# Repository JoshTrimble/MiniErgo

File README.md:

This design was inspired by the Gboards' GergoPlex. I wanted to take the base design and tweak it to be a smaller form factor, while maintaining the layout as much as possible. This board is driven by 2 Xiao Seeed Studio RP2040s and includes hot swappable sockets for Kailh Choc switches. The PCB is designed yp be double sided with the left side having the micro control placed upside down via standoffs.

One other thing to note; Because of the minimal footprint achieved, there might be a very slight overhang of the outer hot swap socket solder points and the edge of the board depending on the hot swap sockets used. There should be plenty of room for contact of the PCB tracks to the socket, and the excess can be sanded down to be flush with the PCB if desired. From my testing, you can't even notice. This design might be changed in future versions of the board. (P.S. Know that sanding PCBs can be hazardous. Please take procautions if you choose to sand anything attached to the board)

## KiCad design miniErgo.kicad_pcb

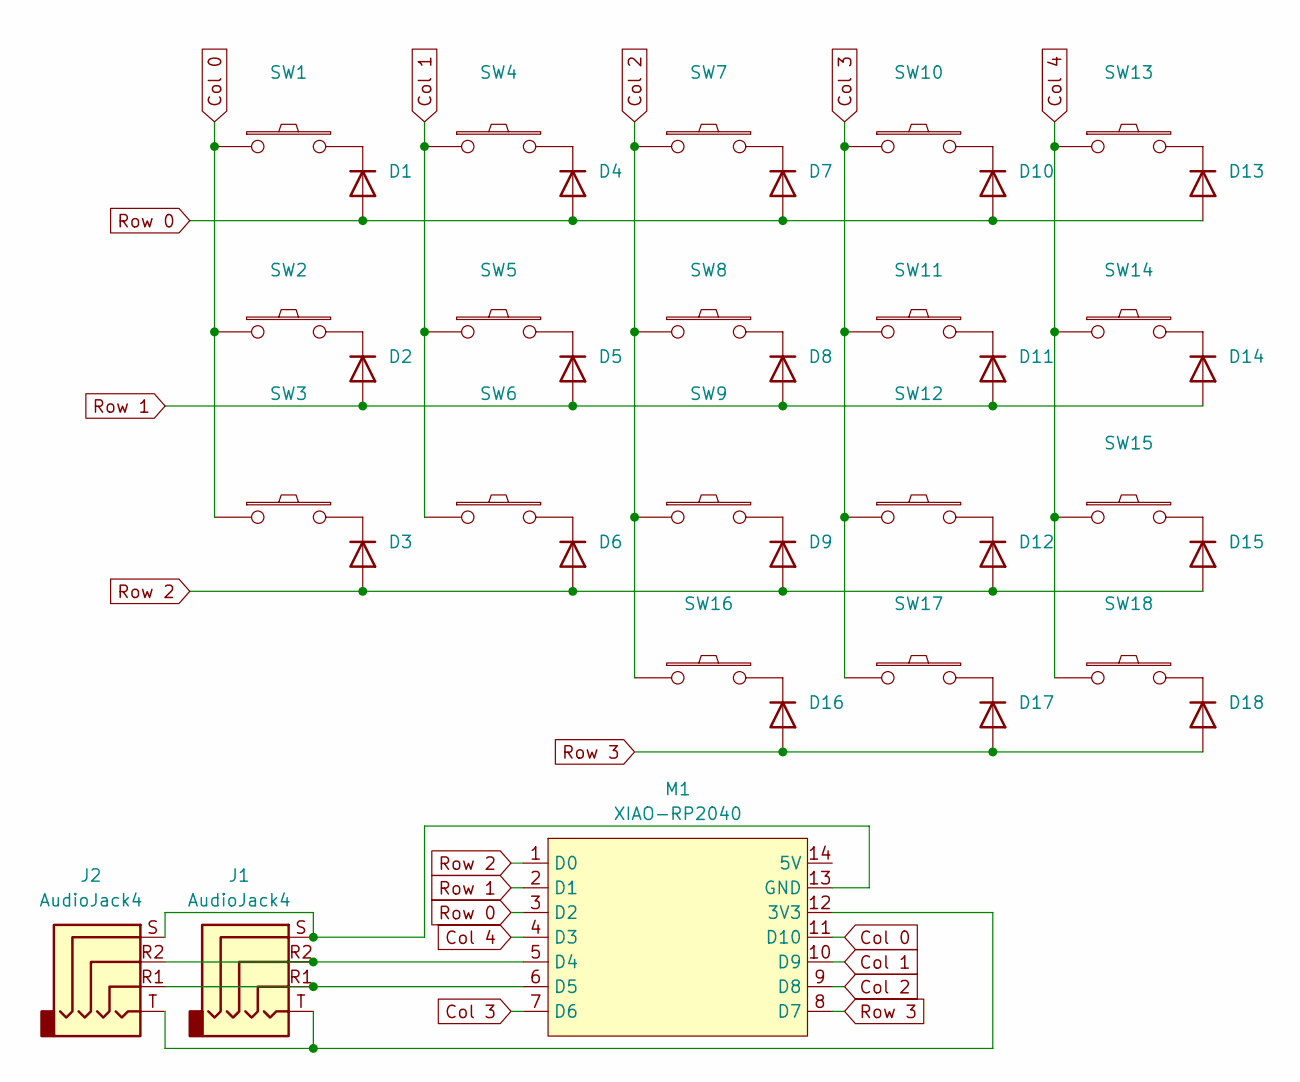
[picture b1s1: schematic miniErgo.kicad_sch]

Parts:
D1, D2, D3, D4, D5, D6, D7, D8, D9, D10, D11, D12, D13, D14, D15, D16, D17, D18: SOD-123F Double Sided
J1, J2: AudioJack4; TRRS-PJ-320A
M1: XIAO-RP2040
SW1, SW2, SW3, SW4, SW5, SW6, SW7, SW8, SW9, SW10, SW11, SW12, SW13, SW14, SW15, SW16, SW17, SW18: Kailh Choch HS Double Sided

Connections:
Col 0: M1.11 (D10), SW1.1, SW2.1, SW3.1
Col 1: M1.10 (D9), SW4.1, SW5.1, SW6.1
Col 2: M1.9 (D8), SW7.1, SW8.1, SW9.1, SW16.1
Col 3: M1.7 (D6), SW10.1, SW11.1, SW12.1, SW17.1
Col 4: M1.4 (D3), SW13.1, SW14.1, SW15.1, SW18.1
unnamed: D1.1 (K), SW1.2
unnamed: D2.1 (K), SW2.2
unnamed: D3.1 (K), SW3.2
unnamed: D4.1 (K), SW4.2
unnamed: D5.1 (K), SW5.2
unnamed: D6.1 (K), SW6.2
unnamed: D7.1 (K), SW7.2
unnamed: D8.1 (K), SW8.2
unnamed: D9.1 (K), SW9.2
unnamed: D10.1 (K), SW10.2
unnamed: D11.1 (K), SW11.2
unnamed: D12.1 (K), SW12.2
unnamed: D13.1 (K), SW13.2
unnamed: D14.1 (K), SW14.2
unnamed: D15.1 (K), SW15.2
unnamed: D16.1 (K), SW16.2
unnamed: D17.1 (K), SW17.2
unnamed: D18.1 (K), SW18.2
unnamed: J1.R1, J2.R1, M1.6 (D5)
unnamed: J1.R2, J2.R2, M1.5 (D4)
unnamed: J1.S, J2.S, M1.13 (GND)
unnamed: J1.T, J2.T, M1.12 (3V3)
Row 0: D1.2 (A), D4.2 (A), D7.2 (A), D10.2 (A), D13.2 (A), M1.3 (D2)
Row 1: D2.2 (A), D5.2 (A), D8.2 (A), D11.2 (A), D14.2 (A), M1.2 (D1)
Row 2: D3.2 (A), D6.2 (A), D9.2 (A), D12.2 (A), D15.2 (A), M1.1 (D0)
Row 3: D16.2 (A), D17.2 (A), D18.2 (A), M1.8 (D7)

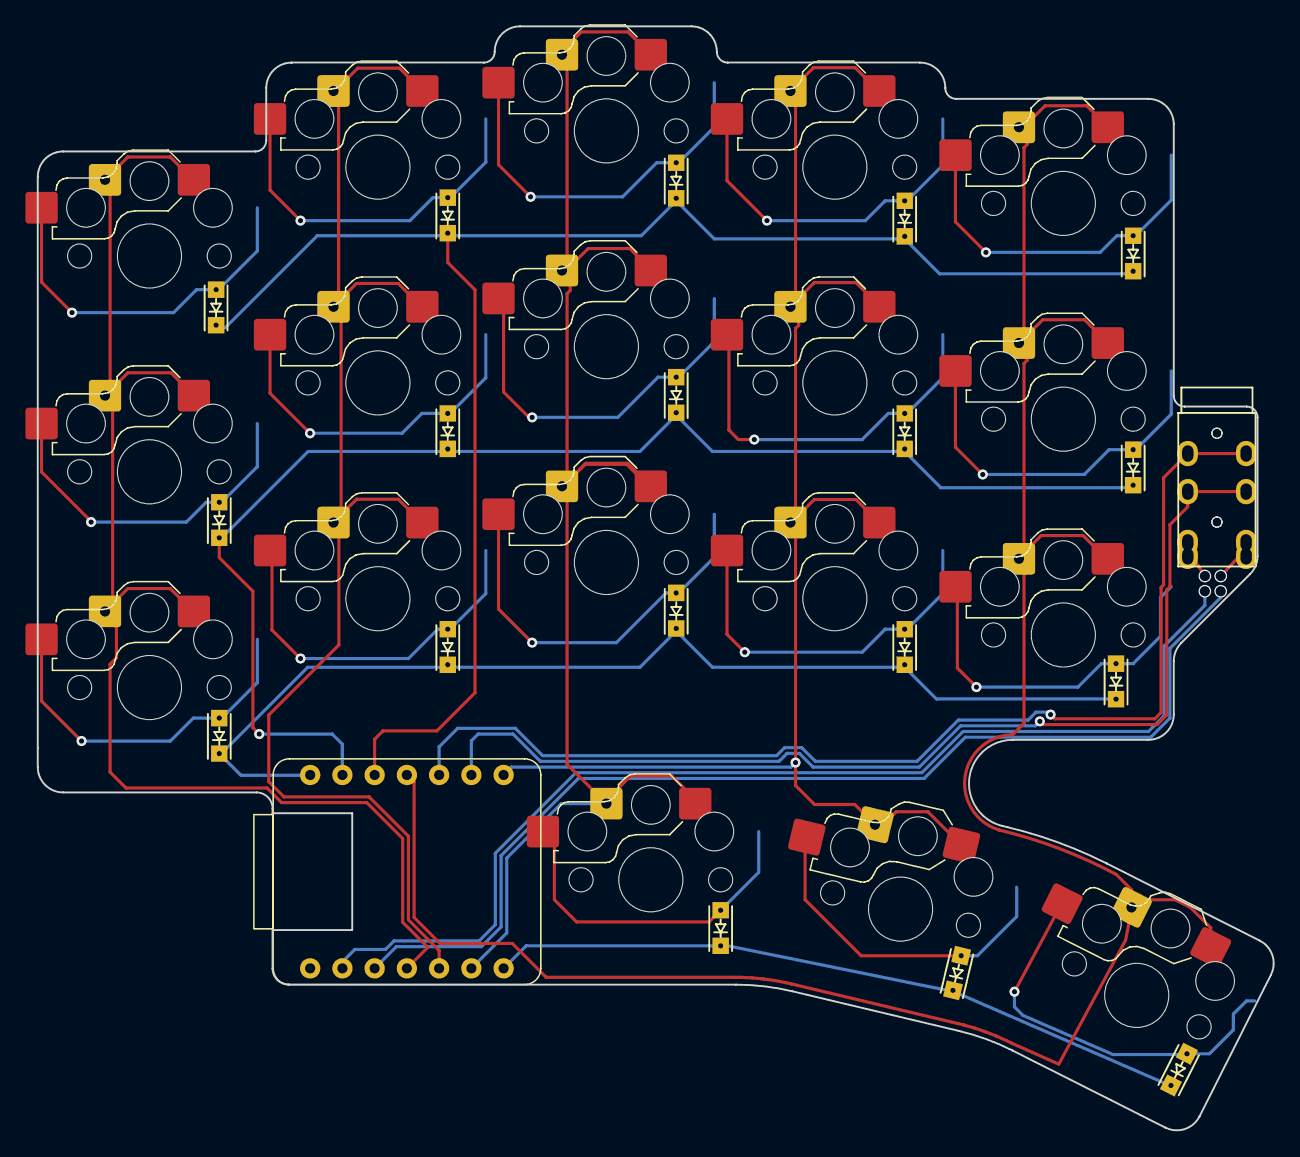
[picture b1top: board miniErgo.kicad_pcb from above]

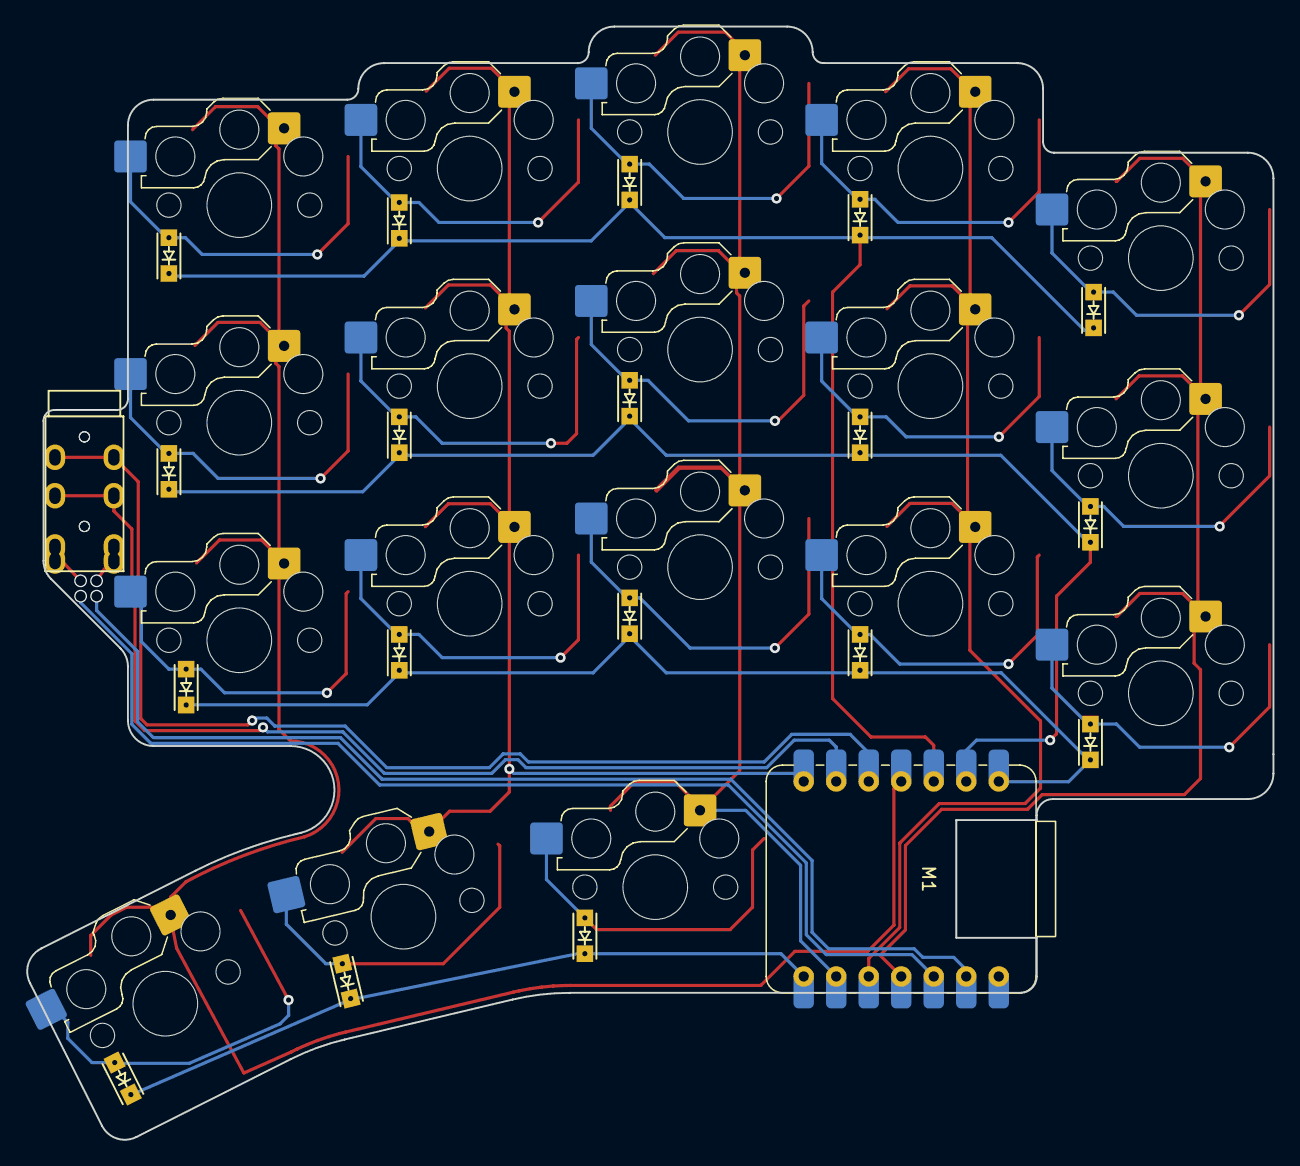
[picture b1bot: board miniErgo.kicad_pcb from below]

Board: 2 copper layers, 97.4 x 87.0 mm, 39 parts (20 on the bottom side), 31 nets.
